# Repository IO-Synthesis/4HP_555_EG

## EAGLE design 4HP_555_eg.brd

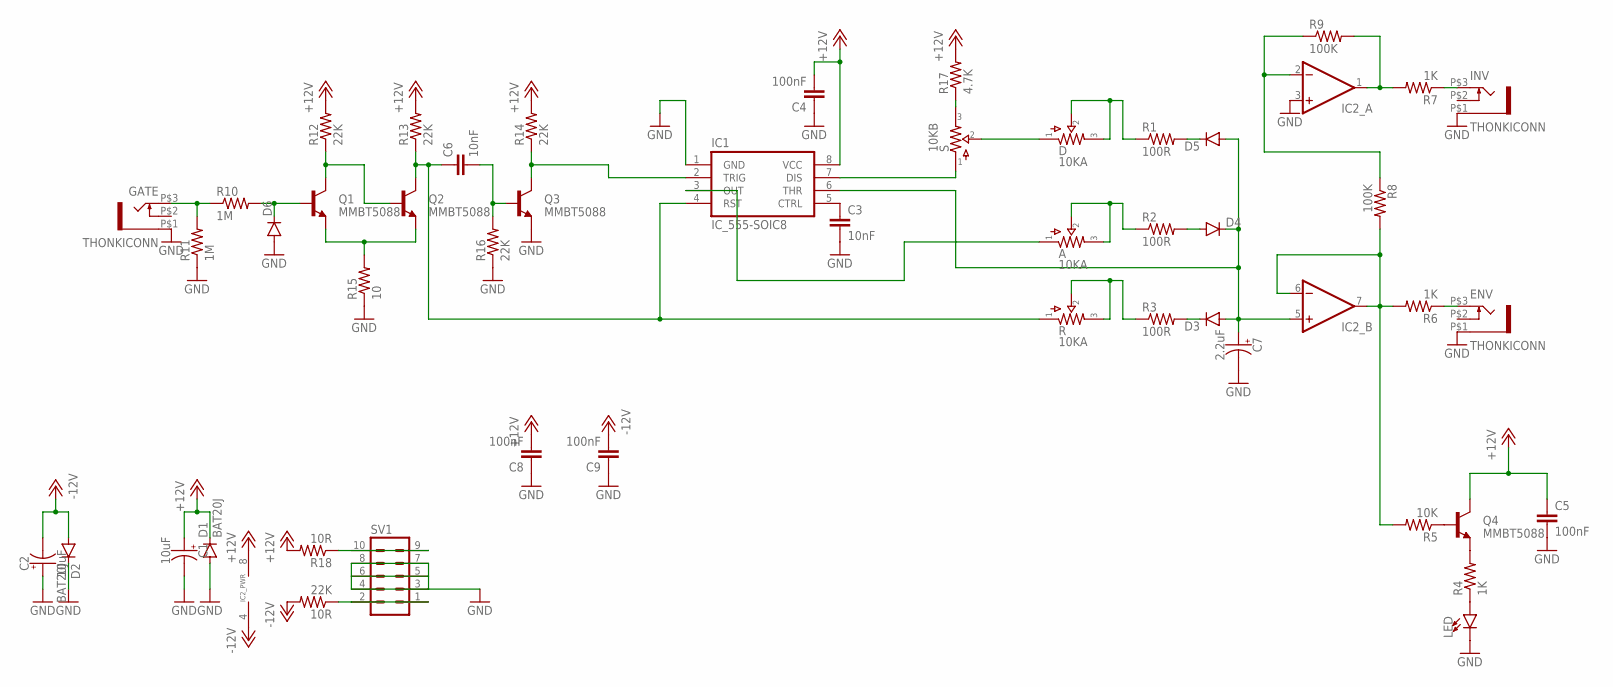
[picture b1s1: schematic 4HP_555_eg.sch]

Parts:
10R: 22K; 0603-RES
A: 10KA; 9MM_W/MOUNTS-2MMHOLES
C1, C2: 10uF; 050_020_1
C3, C6: 10nF; 0603-CAP
C4, C5, C8, C9: 100nF; 0603-CAP
C7: 2.2uF; 050_020_1
D: 10KA; 9MM_W/MOUNTS-2MMHOLES
D1, D2: BAT20J; SOD-123
D3, D4, D5, D6: DIODESOD; SOD-323
ENV: THONKICONN
GATE: THONKICONN
IC1: IC_555-SOIC8; SOIC-8
IC2: DUALSMD; SO08
INV: THONKICONN
LED: LED5MM; LED_5MM
Q1, Q2, Q3, Q4: MMBT5088; SOT23
R: 10KA; 9MM_W/MOUNTS-2MMHOLES
R1, R2, R3: 100R; 0603-RES
R4, R6, R7: 1K; 0603-RES
R5: 10K; 0603-RES
R8, R9: 100K; 0603-RES
R10, R11: 1M; 0603-RES
R12, R13, R14, R16: 22K; 0603-RES
R15: 10; 0603-RES
R17: 4.7K; 0603-RES
R18: 10R; 0603-RES
S: 10KB; 9MM_W/MOUNTS-2MMHOLES
SV1: EURO_POWER_HEADER

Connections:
+12V: C1.+, C4.2, C5.1, C8.2, D1.C, IC1.8 (VCC), IC2.8 (V+), Q4.3 (C), R12.2, R13.2, R14.2, R17.2, R18.2
-12V: 10R.2, C2.-, C9.2, D2.A, IC2.4 (V-)
CTRL: C3.1, IC1.5 (CTRL)
GND: C1.-, C2.+, C3.2, C4.1, C5.2, C7.-, C8.1, C9.1, D1.A, D2.C, D6.A, ENV.P$1 (5), GATE.P$1 (5), IC1.1 (GND), IC2.3 (+IN), INV.P$1 (5), LED.K (C), Q3.2 (E), R11.1, R15.1, R16.1, SV1.3, SV1.4, SV1.5, SV1.6, SV1.7, SV1.8
unnamed: IC2.6 (-IN), IC2.7 (OUT), R5.2, R6.2, R8.2
unnamed: C7.+, D3.A, D4.C, D5.A, IC1.6 (THR), IC2.5 (+IN)
unnamed: D5.C, R1.2
unnamed: D4.A, R2.2
unnamed: D3.C, R3.2
unnamed: D.P$2 (2), D.P$3 (3), R1.1
unnamed: A.P$2 (2), A.P$3 (3), R2.1
unnamed: R.P$2 (2), R.P$3 (3), R3.1
unnamed: Q4.2 (E), R4.2
unnamed: LED.A, R4.1
unnamed: R18.1, SV1.9, SV1.10
unnamed: 10R.1, SV1.1, SV1.2
unnamed: D.P$1 (1), S.P$2 (2)
unnamed: IC1.7 (DIS), S.P$1 (1)
unnamed: A.P$1 (1), IC1.3 (OUT)
unnamed: IC1.2 (TRIG), Q3.3 (C), R14.1
unnamed: Q1.3 (C), Q2.1 (B), R12.1
unnamed: Q4.1 (B), R5.1
unnamed: ENV.P$3 (3), R6.1
unnamed: INV.P$3 (3), R7.1
unnamed: IC2.1 (OUT), R7.2, R9.2
unnamed: IC2.2 (-IN), R8.1, R9.1
unnamed: Q1.2 (E), Q2.2 (E), R15.2
unnamed: GATE.P$3 (3), R10.1, R11.2
unnamed: D6.C, Q1.1 (B), R10.2
unnamed: C6.1, IC1.4 (RST), Q2.3 (C), R.P$1 (1), R13.1
unnamed: C6.2, Q3.1 (B), R16.2
unnamed: R17.1, S.P$3 (3)

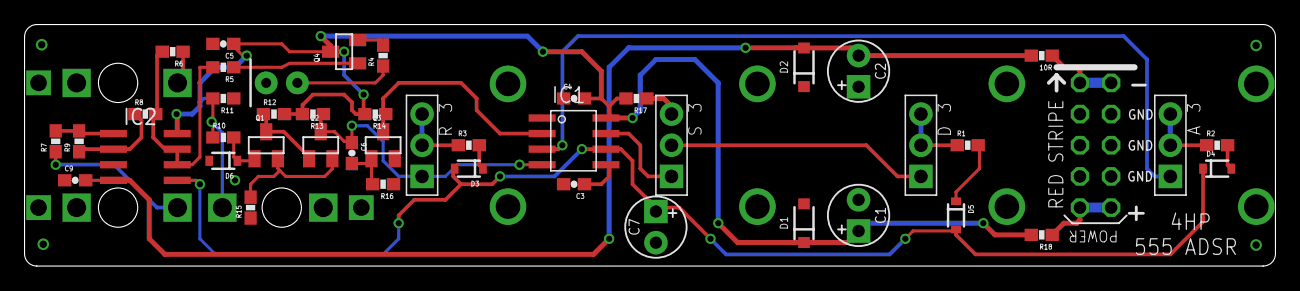
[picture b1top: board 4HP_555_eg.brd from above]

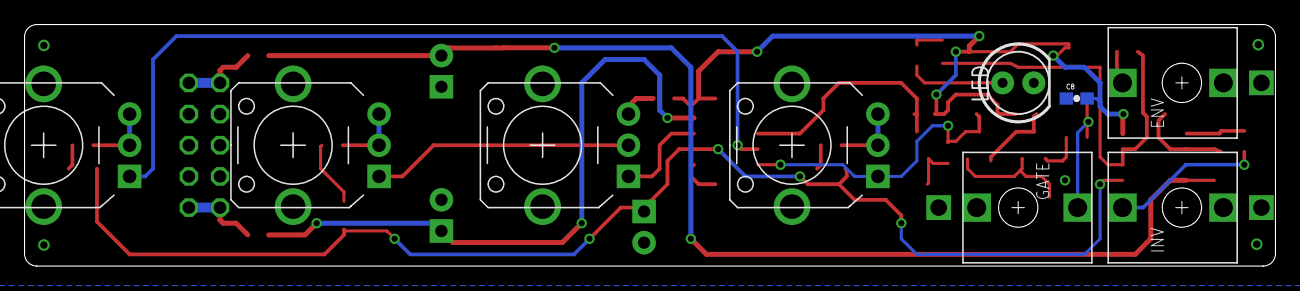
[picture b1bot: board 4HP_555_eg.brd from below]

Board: 2 copper layers, 101.9 x 19.7 mm, 49 parts (5 on the bottom side), 32 nets.

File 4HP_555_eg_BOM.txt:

Partlist exported from C:/Users/Erik/Documents/GitHub/4HP_555_EG/4HP_555_eg.sch at 4/30/2017 8:28 AM

Part Value        Device                 Package               Description     PROD_ID     VALUE   
10R  22K          RESISTOR0603-RES       0603-RES              Resistor                            
A    10KA         POTS9MM_MOUNTED_2MMH   9MM_W/MOUNTS-2MMHOLES                                     
C1   10uF         0501                   050_020_1             0.22 - 100uF                        
C2   10uF         0501                   050_020_1             0.22 - 100uF                        
C3   10nF         CAP0603-CAP            0603-CAP              Capacitor                           
C4   100nF        CAP0603-CAP            0603-CAP              Capacitor                           
C5   100nF        CAP0603-CAP            0603-CAP              Capacitor                           
C6   10nF         CAP0603-CAP            0603-CAP              Capacitor                           
C7   2.2uF        0501                   050_020_1             0.22 - 100uF                        
C8   100nF        CAP0603-CAP            0603-CAP              Capacitor                           
C9   100nF        CAP0603-CAP            0603-CAP              Capacitor                           
D    10KA         POTS9MM_MOUNTED_2MMH   9MM_W/MOUNTS-2MMHOLES                                     
D1   BAT20J       DIODESOD123            SOD-123               Diode                               
D2   BAT20J       DIODESOD123            SOD-123               Diode                               
D3                DIODESOD               SOD-323               Diode           DIO-09646           
D4                DIODESOD               SOD-323               Diode           DIO-09646           
D5                DIODESOD               SOD-323               Diode           DIO-09646           
D6                DIODESOD               SOD-323               Diode           DIO-09646           
ENV  THONKICONN   THONKICONN             THONKICONN                                                
GATE THONKICONN   THONKICONN             THONKICONN                                                
IC1  IC_555-SOIC8 IC_555-SOIC8           SOIC-8                Classic 555 IC                      
IC2               DUALSMD                SO08                  OP AMP                              
INV  THONKICONN   THONKICONN             THONKICONN                                                
LED               LED5MM                 LED_5MM               LED (Generic)                       
Q1   MMBT5088     TRANSISTOR_NPNMMBT5088 SOT23                 Generic NPN BJT TRANS-11160 MMBT5088
Q2   MMBT5088     TRANSISTOR_NPNMMBT5088 SOT23                 Generic NPN BJT TRANS-11160 MMBT5088
Q3   MMBT5088     TRANSISTOR_NPNMMBT5088 SOT23                 Generic NPN BJT TRANS-11160 MMBT5088
Q4   MMBT5088     TRANSISTOR_NPNMMBT5088 SOT23                 Generic NPN BJT TRANS-11160 MMBT5088
R    10KA         POTS9MM_MOUNTED_2MMH   9MM_W/MOUNTS-2MMHOLES                                     
R1   100R         RESISTOR0603-RES       0603-RES              Resistor                            
R2   100R         RESISTOR0603-RES       0603-RES              Resistor                            
R3   100R         RESISTOR0603-RES       0603-RES              Resistor                            
R4   1K           RESISTOR0603-RES       0603-RES              Resistor                            
R5   10K          RESISTOR0603-RES       0603-RES              Resistor                            
R6   1K           RESISTOR0603-RES       0603-RES              Resistor                            
R7   1K           RESISTOR0603-RES       0603-RES              Resistor                            
R8   100K         RESISTOR0603-RES       0603-RES              Resistor                            
R9   100K         RESISTOR0603-RES       0603-RES              Resistor                            
R10  1M           RESISTOR0603-RES       0603-RES              Resistor                            
R11  1M           RESISTOR0603-RES       0603-RES              Resistor                            
R12  22K          RESISTOR0603-RES       0603-RES              Resistor                            
R13  22K          RESISTOR0603-RES       0603-RES              Resistor                            
R14  22K          RESISTOR0603-RES       0603-RES              Resistor                            
R15  10           RESISTOR0603-RES       0603-RES              Resistor                            
R16  22K          RESISTOR0603-RES       0603-RES              Resistor                            
R17  4.7K         RESISTOR0603-RES       0603-RES              Resistor                            
R18  10R          RESISTOR0603-RES       0603-RES              Resistor                            
S    10KB         POTS9MM_MOUNTED_2MMH   9MM_W/MOUNTS-2MMHOLES                                     
SV1               EURO_POWER_HEADER      EURO_POWER_HEADER     Power Header

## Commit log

2017-01-09 :confetti_ball: Added .gitattributes & .gitignore files
2017-03-18 4 HP LM555 Envelope Generator
2017-05-11 4HP 555 ADSR EG
    LM555 ADSR Envelope Generator
2017-05-21 4HP 555 Envelope Generator Panel

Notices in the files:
parts and their libraries:
SparkFun-DiscreteSemi: Licensing: Creative Commons ShareAlike 4.0 International - https://creativecommons.org/licenses/by-sa/4.0
